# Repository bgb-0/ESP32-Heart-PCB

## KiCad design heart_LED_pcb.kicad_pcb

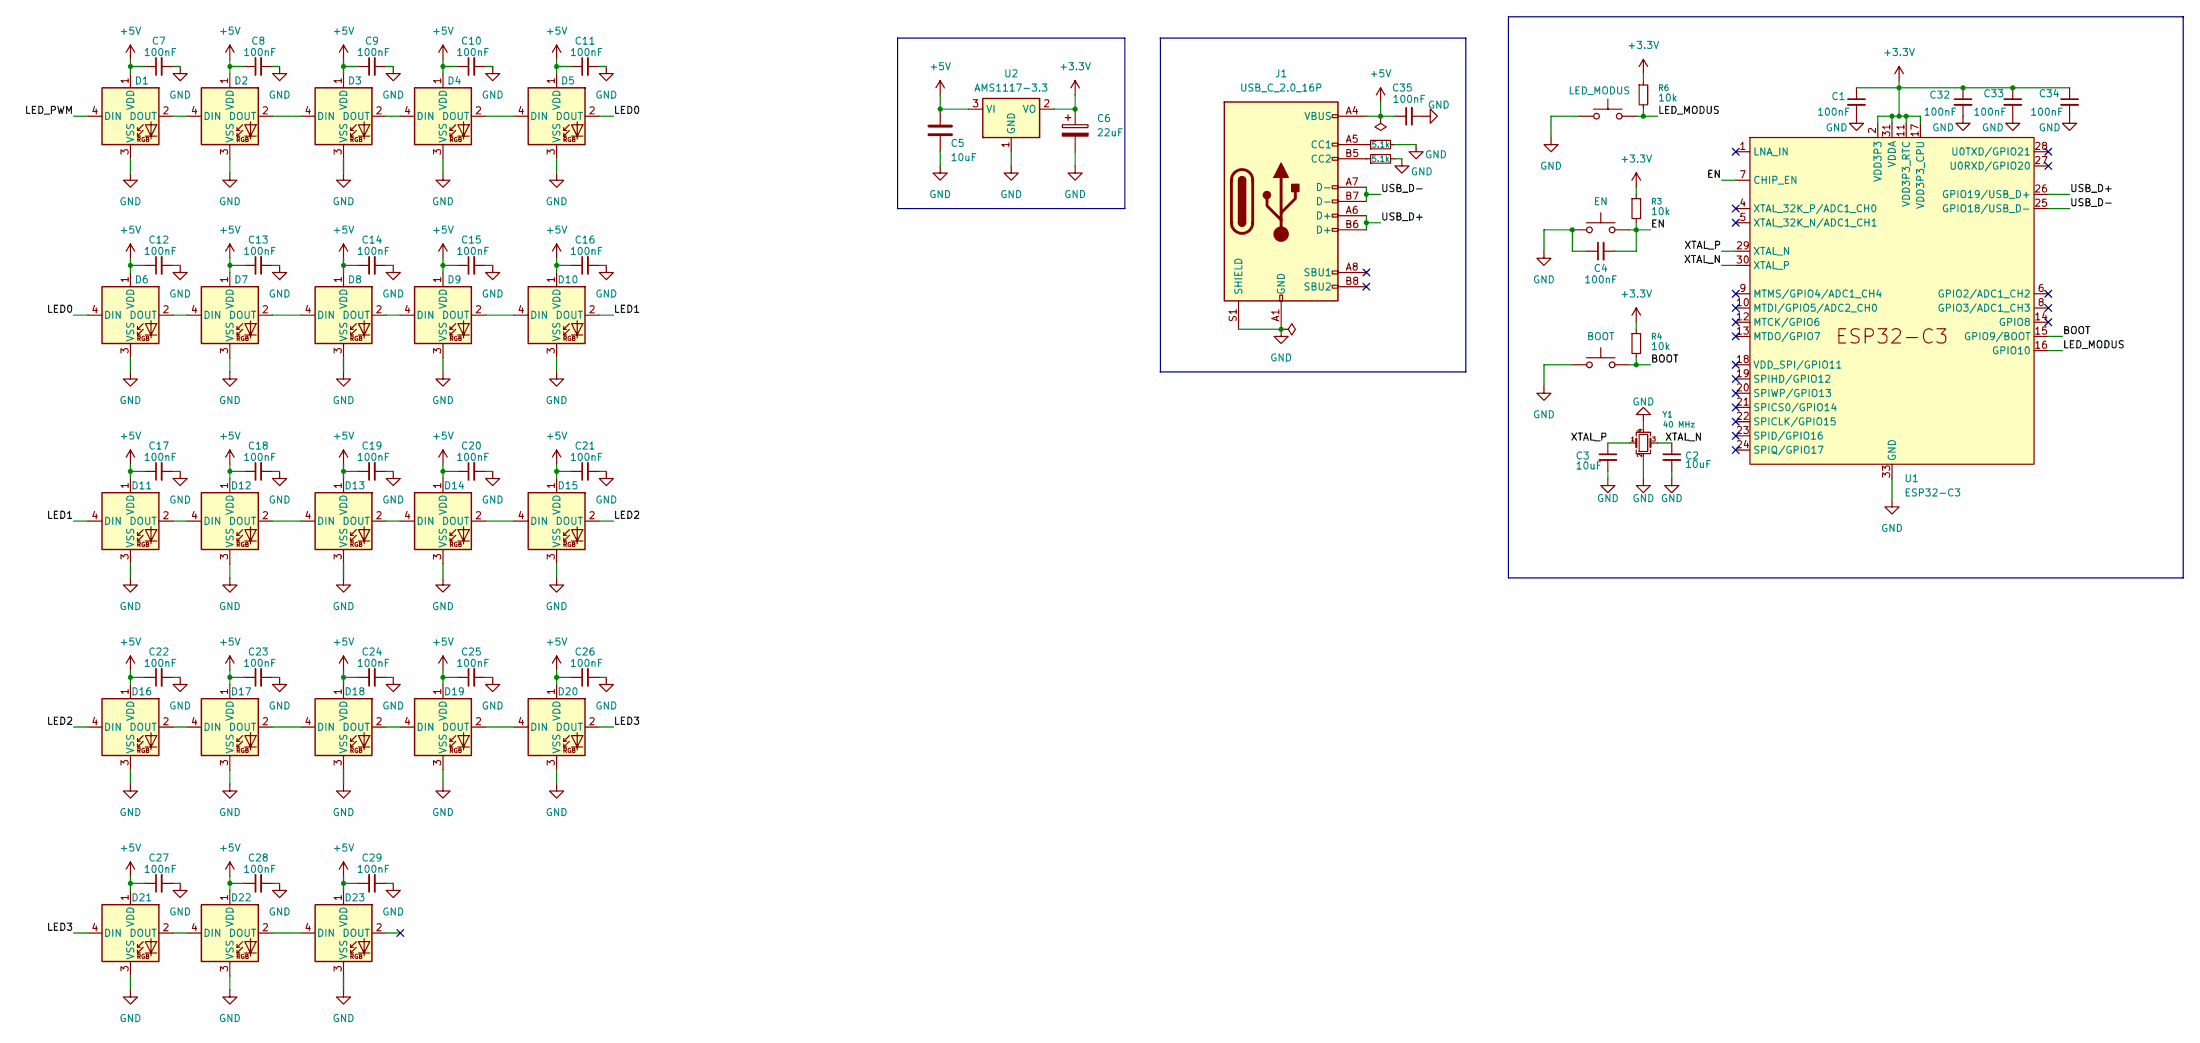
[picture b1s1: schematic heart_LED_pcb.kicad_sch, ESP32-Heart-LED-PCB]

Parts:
C1, C4, C35: 100nF; C_0402_1005Metric
C2, C3: 10uF; C_0805_2012Metric
C5: 10uF; C_0402_1005Metric
C6: 22uF; CP_EIA-3216-18_Kemet-A
C7, C8, C9, C10, C11, C12, C13, C14, C15, C16, C17, C18, C19, C20, C21, C22, C23, C24, C25, C26, C27, C28, C29, C32, C33, C34: 100nF; C_0805_2012Metric
D1, D2, D3, D4, D5, D6, D7, D8, D9, D10, D11, D12, D13, D14, D15, D16, D17, D18, D19, D20, D21, D22, D23: WS2812B; LED_WS2812B_PLCC4_5.0x5.0mm_P3.2mm
J1: USB_C_2.0_16P; USB_C_Receptacle_G-Switch_GT-USB-7010ASV
R1, R2: 5.1k; R_0603_1608Metric
R3, R4, R6: 10k; R_0402_1005Metric
SW1: EN; SW_Push_SPST_NO_Alps_SKRK
SW2: BOOT; SW_Push_SPST_NO_Alps_SKRK
SW3: LED_MODUS; SW_Push_SPST_NO_Alps_SKRK
U1: ESP32-C3; QFN-32-1EP_5x5mm_P0.5mm_EP3.45x3.45mm
U2: AMS1117-3.3; SOT-223-3_TabPin2
Y1: 40 MHz; Crystal_SMD_TXC_7M-4Pin_3.2x2.5mm

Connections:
+3.3V: C1.1, C6.1, C32.1, C33.1, C34.1, R3.1, R4.1, R6.1, U1.2 (VDD3P3), U1.3 (VDD3P3), U1.11 (VDD3P3_RTC), U1.17 (VDD3P3_CPU), U1.31 (VDDA), U1.32 (VDDA), U2.2 (VO)
+5V: C5.1, C7.1, C8.1, C9.1, C10.1, C11.1, C12.1, C13.1, C14.1, C15.1, C16.1, C17.1, C18.1, C19.1, C20.1, C21.1, C22.1, C23.1, C24.1, C25.1, C26.1, C27.1, C28.1, C29.1, C35.1, D1.1 (VDD), D2.1 (VDD), D3.1 (VDD), D4.1 (VDD), D5.1 (VDD), D6.1 (VDD), D7.1 (VDD), D8.1 (VDD), D9.1 (VDD), D10.1 (VDD), D11.1 (VDD), D12.1 (VDD), D13.1 (VDD), D14.1 (VDD), D15.1 (VDD), D16.1 (VDD), D17.1 (VDD), D18.1 (VDD), D19.1 (VDD), D20.1 (VDD), D21.1 (VDD), D22.1 (VDD), D23.1 (VDD), J1.A4 (VBUS), J1.A9 (VBUS), J1.B4 (VBUS), J1.B9 (VBUS), U2.3 (VI)
/BOOT: R4.2, SW2.2, U1.15 (GPIO9/BOOT)
/EN: C4.2, R3.2, SW1.2, U1.7 (CHIP_EN)
/LED0: D5.2 (DOUT), D6.4 (DIN)
/LED1: D10.2 (DOUT), D11.4 (DIN)
/LED2: D15.2 (DOUT), D16.4 (DIN)
/LED3: D20.2 (DOUT), D21.4 (DIN)
/LED_MODUS: R6.2, SW3.2, U1.16 (GPIO10)
/LED_PWM: D1.4 (DIN)
/USB_D+: J1.A6 (D+), J1.B6 (D+), U1.26 (GPIO19/USB_D+)
/USB_D-: J1.A7 (D-), J1.B7 (D-), U1.25 (GPIO18/USB_D-)
/XTAL_N: C2.1, U1.30 (XTAL_P), Y1.3
/XTAL_P: C3.1, U1.29 (XTAL_N), Y1.1
GND: C1.2, C2.2, C3.2, C4.1, C5.2, C6.2, C7.2, C8.2, C9.2, C10.2, C11.2, C12.2, C13.2, C14.2, C15.2, C16.2, C17.2, C18.2, C19.2, C20.2, C21.2, C22.2, C23.2, C24.2, C25.2, C26.2, C27.2, C28.2, C29.2, C32.2, C33.2, C34.2, C35.2, D1.3 (VSS), D2.3 (VSS), D3.3 (VSS), D4.3 (VSS), D5.3 (VSS), D6.3 (VSS), D7.3 (VSS), D8.3 (VSS), D9.3 (VSS), D10.3 (VSS), D11.3 (VSS), D12.3 (VSS), D13.3 (VSS), D14.3 (VSS), D15.3 (VSS), D16.3 (VSS), D17.3 (VSS), D18.3 (VSS), D19.3 (VSS), D20.3 (VSS), D21.3 (VSS), D22.3 (VSS), D23.3 (VSS), J1.A1 (GND), J1.A12 (GND), J1.B1 (GND), J1.B12 (GND), J1.S1 (SHIELD), R1.2, R2.2, SW1.1, SW2.1, SW3.1, U1.33 (GND), U2.1 (GND), Y1.2, Y1.4
unnamed: D1.2 (DOUT), D2.4 (DIN)
unnamed: D2.2 (DOUT), D3.4 (DIN)
unnamed: D3.2 (DOUT), D4.4 (DIN)
unnamed: D4.2 (DOUT), D5.4 (DIN)
unnamed: D6.2 (DOUT), D7.4 (DIN)
unnamed: D7.2 (DOUT), D8.4 (DIN)
unnamed: D8.2 (DOUT), D9.4 (DIN)
unnamed: D9.2 (DOUT), D10.4 (DIN)
unnamed: D11.2 (DOUT), D12.4 (DIN)
unnamed: D12.2 (DOUT), D13.4 (DIN)
unnamed: D13.2 (DOUT), D14.4 (DIN)
unnamed: D14.2 (DOUT), D15.4 (DIN)
unnamed: D16.2 (DOUT), D17.4 (DIN)
unnamed: D17.2 (DOUT), D18.4 (DIN)
unnamed: D18.2 (DOUT), D19.4 (DIN)
unnamed: D19.2 (DOUT), D20.4 (DIN)
unnamed: D21.2 (DOUT), D22.4 (DIN)
unnamed: D22.2 (DOUT), D23.4 (DIN)
unnamed: J1.A5 (CC1), R1.1
unnamed: J1.B5 (CC2), R2.1

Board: 4 copper layers, 68 parts (0 on the bottom side), 34 nets, no tracks yet.

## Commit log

2025-04-05 Update LICENSE
2025-04-20 Add original files from laptop
2025-06-15 Adding KiCad project files
2025-06-15 Updated schematic
